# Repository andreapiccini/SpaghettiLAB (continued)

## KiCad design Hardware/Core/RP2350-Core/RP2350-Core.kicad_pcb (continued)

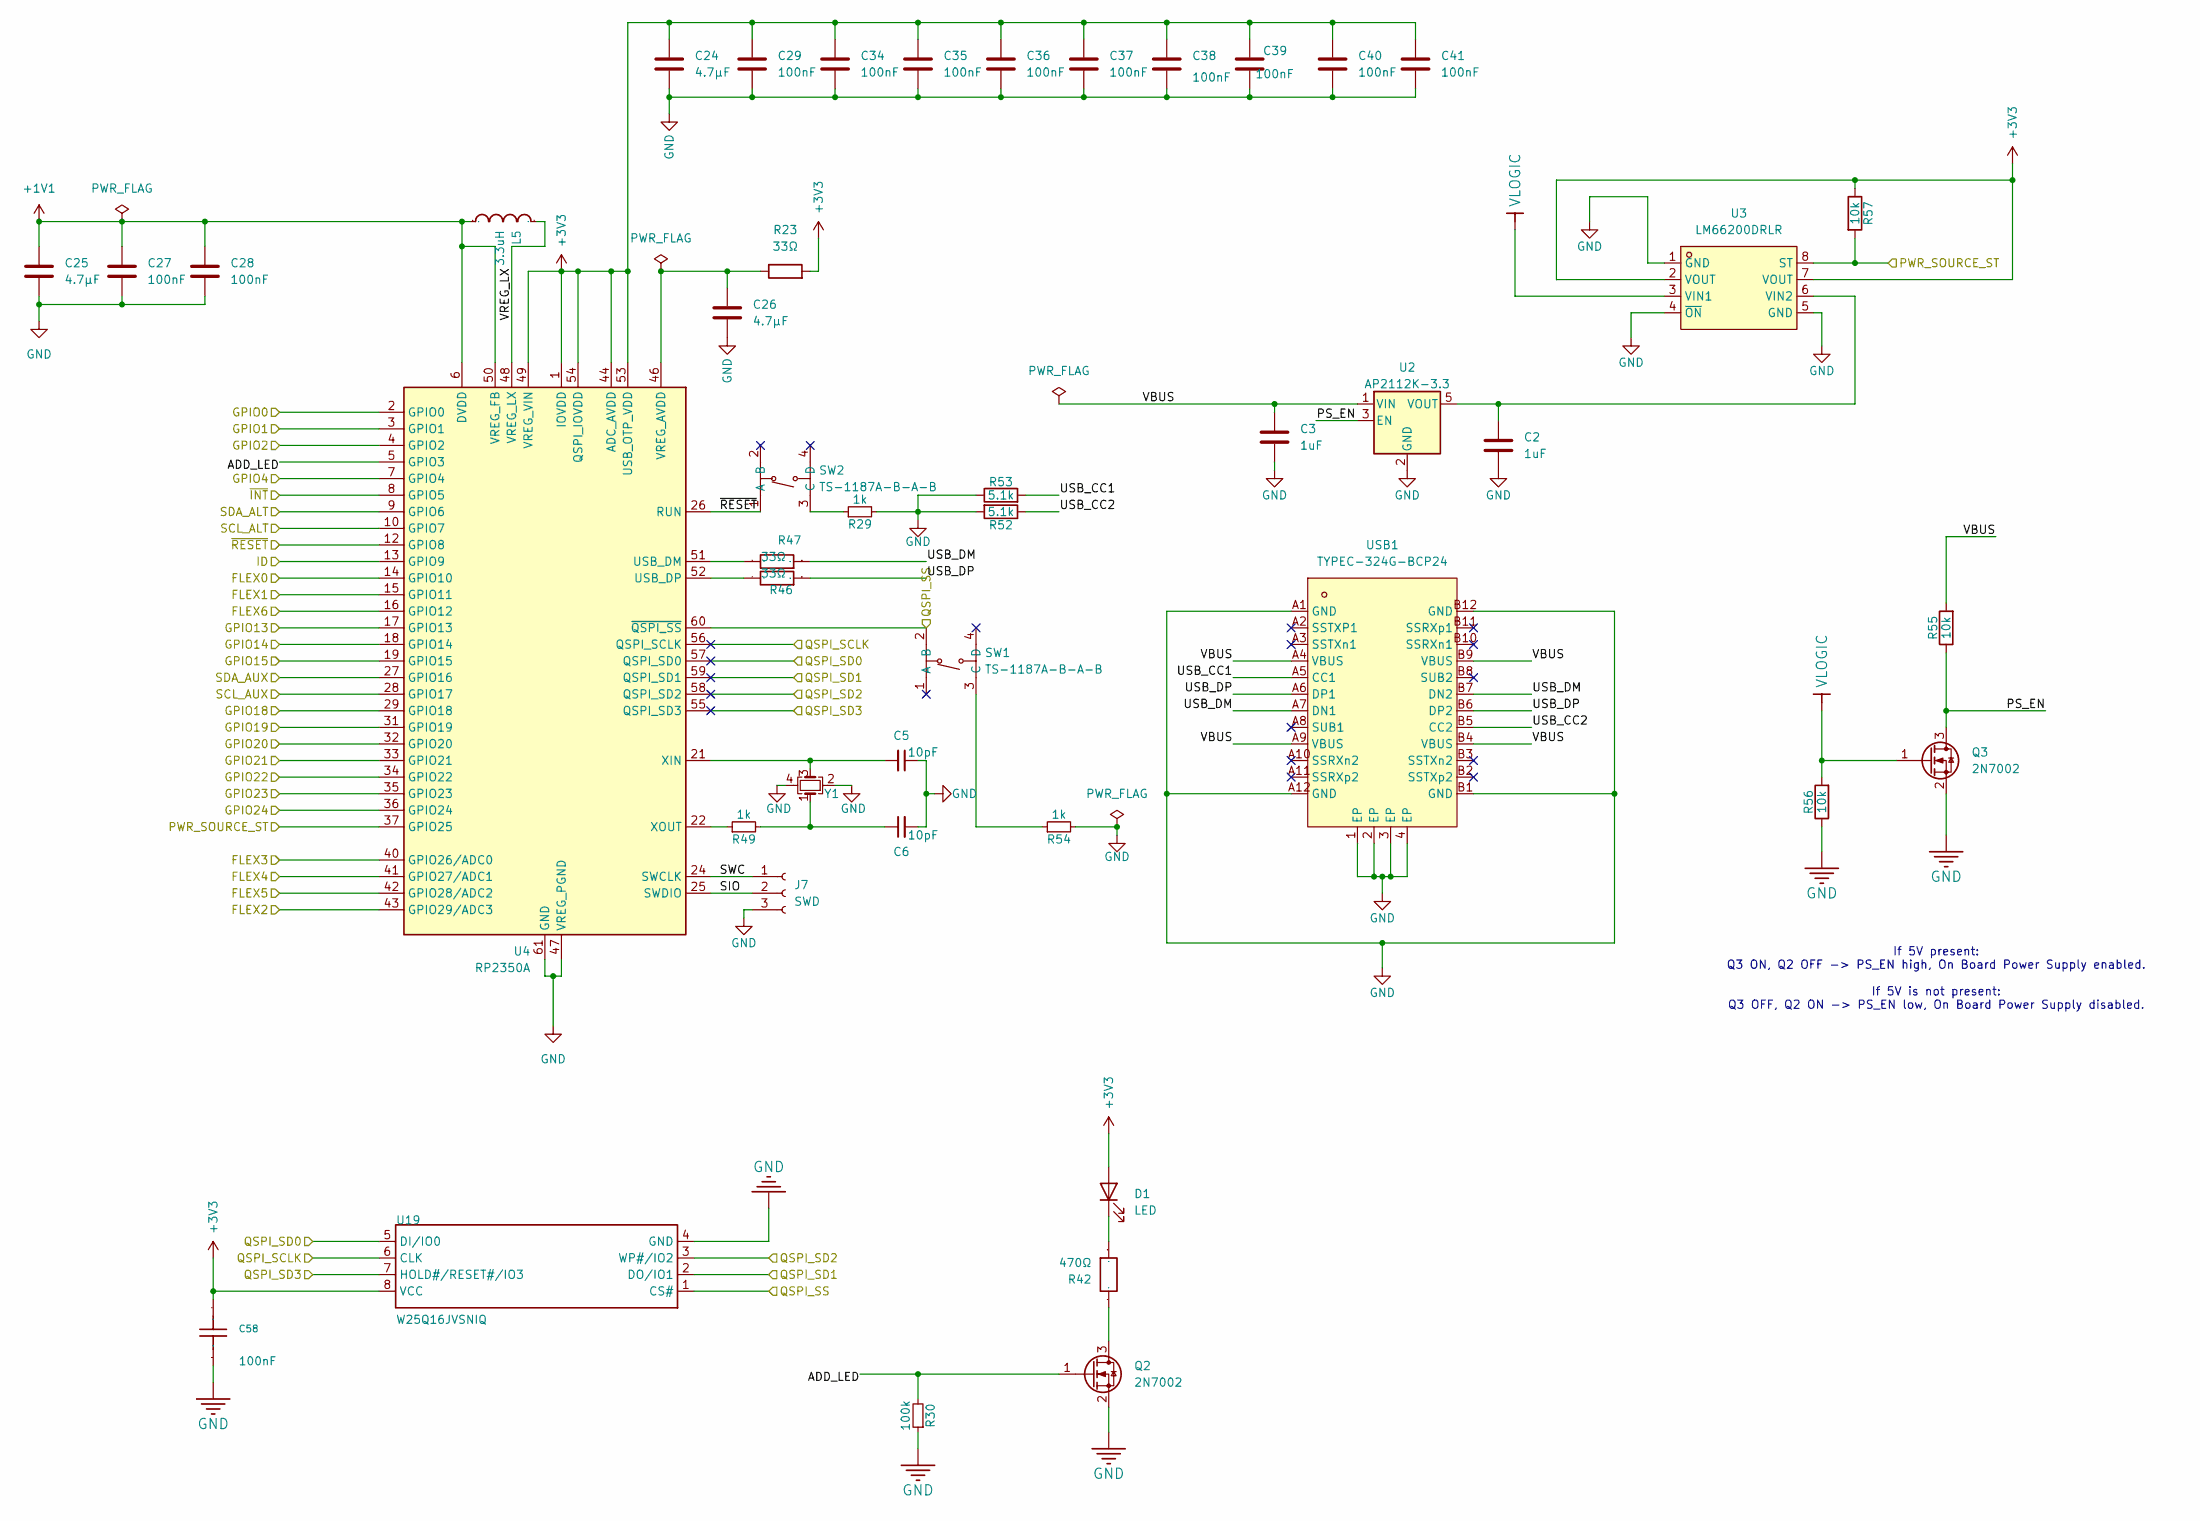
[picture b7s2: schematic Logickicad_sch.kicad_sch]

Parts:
C2, C3: 1uF; C0603; MPN CL05B104KA5NNNC
C5, C6: 10pF; C0603; MPN CL10C100JB8NFNC
C24, C25, C26: 4.7μF; C0603; MPN GRM155D80E475ME47J
C27, C28, C29, C34, C35, C36, C37, C38, C39, C40, C41: 100nF; C0603; MPN CL05B104KA5NNNC
C58: 100nF; C0603; Manufacturer Part 1206B104K500CT; LCSC Part Name 100nF ±10% 50V
D1: LED; LED0603-RD
J7: SWD; PinHeader_1x03_P1.27mm_Vertical
L5: 3.3uH; L1210; Manufacturer Part CMI322513U3R3KT; LCSC Part Name 3.3uH ±10%
Q2, Q3: 2N7002; SOT-23-3_L2.9-W1.3-P1.90-LS2.4-BR
R23: 33Ω; R0603; MPN RC0402FR-0733RL
R29, R49, R54: 1k; R0603; MPN RT0603FRE101KL
R30: 100k; R0603; MPN RT0603FRE101KL
R42: 470Ω; R0603; Manufacturer Part FRC0805J103TS; LCSC Part Name 10kΩ ±5% 125mW 厚膜电阻
R46, R47: 33Ω; R0603; Manufacturer Part CR0805F827R0G; LCSC Part Name 厚膜电阻 27Ω ±1% 125mW
R52, R53: 5.1k; R0603; MPN RC0402FR-075K1L
R55, R56, R57: 10k; R0603; MPN RC0402FR-075K1L
SW1, SW2: TS-1187A-B-A-B; SW-SMD_4P-L5.1-W5.1-P3.70-LS6.5-TL_H1.5; MPN TS-1187A-B-A-B; LCSC Part C318884
U2: AP2112K-3.3; SOT-25-5_L2.9-W1.6-P0.95-LS2.8-BL; MPN AP2112K-3.3TRG1
U3: LM66200DRLR; SOT-583-8_L2.1-W1.2-P0.50-LS1.6-BL; MPN LM66200DRLR; LCSC Part C3235556
U4: RP2350A; QFN-60_L7.0-W7.0-P0.40-TL-EP3.4
U19: W25Q16JVSNIQ; SOP-8_L4.9-W3.9-P1.27-LS6.0-BL; Manufacturer Part W25Q16JVSNIQ; LCSC Part Name 支持双/四路SPI接口的3V、16Mbit 串行闪存
USB1: TYPEC-324G-BCP24; USB-C-SMD_TYPEC-324G-BCP24; MPN TYPEC-324G-BCP24; LCSC Part C920230
Y1: Crystal; CRYSTAL-SMD_4P-L3.2-W2.5-BL; MPN ABM8-272-T3

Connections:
+1V1: C25.1, C27.2, C28.2, L5.1, U4.6 (DVDD), U4.23 (DVDD), U4.39 (DVDD), U4.50 (VREG_FB)
+3V3: C24.1, C29.2, C34.2, C35.2, C36.2, C37.2, C38.2, C39.2, C40.2, C41.2, C58.2, D1.2 (A), R23.2, R57.1, U3.2 (VOUT), U3.7 (VOUT), U4.1 (IOVDD), U4.11 (IOVDD), U4.20 (IOVDD), U4.30 (IOVDD), U4.38 (IOVDD), U4.44 (ADC_AVDD), U4.45 (IOVDD), U4.49 (VREG_VIN), U4.53 (USB_OTP_VDD), U4.54 (QSPI_IOVDD), U19.8 (VCC); also elsewhere on the board
/InOut (page 4)/FLEX0: U4.14 (GPIO10); also elsewhere on the board
/InOut (page 4)/FLEX1: U4.15 (GPIO11); also elsewhere on the board
/InOut (page 4)/FLEX2: U4.43 (GPIO29/ADC3); also elsewhere on the board
/InOut (page 4)/FLEX3: U4.40 (GPIO26/ADC0); also elsewhere on the board
/InOut (page 4)/FLEX4: U4.41 (GPIO27/ADC1); also elsewhere on the board
/InOut (page 4)/FLEX5: U4.42 (GPIO28/ADC2); also elsewhere on the board
/InOut (page 4)/FLEX6: U4.16 (GPIO12); also elsewhere on the board
/InOut (page 4)/GPIO0: U4.2 (GPIO0); also elsewhere on the board
/InOut (page 4)/GPIO1: U4.3 (GPIO1); also elsewhere on the board
/InOut (page 4)/GPIO2: U4.4 (GPIO2); also elsewhere on the board
/InOut (page 4)/GPIO4: U4.7 (GPIO4); also elsewhere on the board
/InOut (page 4)/GPIO13: U4.17 (GPIO13); also elsewhere on the board
/InOut (page 4)/GPIO14: U4.18 (GPIO14); also elsewhere on the board
/InOut (page 4)/GPIO15: U4.19 (GPIO15); also elsewhere on the board
/InOut (page 4)/GPIO18: U4.29 (GPIO18); also elsewhere on the board
/InOut (page 4)/GPIO19: U4.31 (GPIO19); also elsewhere on the board
/InOut (page 4)/GPIO20: U4.32 (GPIO20); also elsewhere on the board
/InOut (page 4)/GPIO21: U4.33 (GPIO21); also elsewhere on the board
/InOut (page 4)/GPIO22: U4.34 (GPIO22); also elsewhere on the board
/InOut (page 4)/GPIO23: U4.35 (GPIO23); also elsewhere on the board
/InOut (page 4)/GPIO24: U4.36 (GPIO24); also elsewhere on the board
/InOut (page 4)/ID: U4.13 (GPIO9); also elsewhere on the board
/InOut (page 4)/QSPI_SCLK: U4.56 (QSPI_SCLK), U19.6 (CLK); also elsewhere on the board
/InOut (page 4)/QSPI_SD0: U4.57 (QSPI_SD0), U19.5 (DI/IO0); also elsewhere on the board
/InOut (page 4)/QSPI_SD1: U4.59 (QSPI_SD1), U19.2 (DO/IO1); also elsewhere on the board
/InOut (page 4)/QSPI_SD2: U4.58 (QSPI_SD2), U19.3 (WP#/IO2); also elsewhere on the board
/InOut (page 4)/QSPI_SD3: U4.55 (QSPI_SD3), U19.7 (HOLD#/RESET#/IO3); also elsewhere on the board
/InOut (page 4)/QSPI_SS: SW1.2 (B), U4.60 (~QSPI_SS), U19.1 (CS#); also elsewhere on the board
/InOut (page 4)/SCL_ALT: U4.10 (GPIO7); also elsewhere on the board
/InOut (page 4)/SCL_AUX: U4.28 (GPIO17); also elsewhere on the board
/InOut (page 4)/SDA_ALT: U4.9 (GPIO6); also elsewhere on the board
/InOut (page 4)/SDA_AUX: U4.27 (GPIO16); also elsewhere on the board
/InOut (page 4)/~INT: U4.8 (GPIO5); also elsewhere on the board
/InOut (page 4)/~RESET: U4.12 (GPIO8); also elsewhere on the board
/Logic/ADD_LED: Q2.1 (G), R30.2, U4.5 (GPIO3)
/Logic/PS_EN: Q3.3 (D), R55.1, U2.3 (EN)
/Logic/PWR_SOURCE_ST: R57.2, U3.8 (ST), U4.37 (GPIO25)
/Logic/SIO: J7.2, U4.25 (SWDIO)
/Logic/SWC: J7.1, U4.24 (SWCLK)
/Logic/USB_CC1: R53.2, USB1.A5 (CC1)
/Logic/USB_CC2: R52.1, USB1.B5 (CC2)
/Logic/USB_DM: R47.1, USB1.A7 (DN1), USB1.B7 (DN2)
/Logic/USB_DP: R46.1, USB1.A6 (DP1), USB1.B6 (DP2)
/Logic/VBUS: C3.2, R55.2, U2.1 (VIN), USB1.A4 (VBUS), USB1.A9 (VBUS), USB1.B4 (VBUS), USB1.B9 (VBUS)
/Logic/VREG_LX: L5.2, U4.48 (VREG_LX)
GND: C2.1, C3.1, C5.1, C6.2, C24.2, C25.2, C26.2, C27.1, C28.1, C29.1, C34.1, C35.1, C36.1, C37.1, C38.1, C39.1, C40.1, C41.1, C58.1, J7.3, Q2.2 (S), Q3.2 (S), R29.2, R30.1, R52.2, R53.1, R54.2, R56.1, U2.2 (GND), U3.1 (GND), U3.4 (~ON), U3.5 (GND), U4.47 (VREG_PGND), U4.61 (GND), U19.4 (GND), USB1.1 (EP), USB1.2 (EP), USB1.3 (EP), USB1.4 (EP), USB1.A1 (GND), USB1.A12 (GND), USB1.B1 (GND), USB1.B12 (GND), Y1.2, Y1.4; also elsewhere on the board
unnamed: C6.1, R49.2, Y1.1
unnamed: D1.1 (K), R42.1
unnamed: Q2.3 (D), R42.2
unnamed: R54.1, SW1.3 (C)
unnamed: SW2.1 (A), U4.26 (RUN)
unnamed: R29.1, SW2.3 (C)
unnamed: C2.2, U2.5 (VOUT), U3.6 (VIN2)
unnamed: R47.2, U4.51 (USB_DM)
unnamed: R46.2, U4.52 (USB_DP)
unnamed: C26.1, R23.1, U4.46 (VREG_AVDD)
unnamed: C5.2, U4.21 (XIN), Y1.3
unnamed: R49.1, U4.22 (XOUT)
VLOGIC: Q3.1 (G), R56.2, U3.3 (VIN1); also elsewhere on the board

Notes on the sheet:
If 5V present: Q3 ON, Q2 OFF -> PS_EN high, On Board Power Supply enabled. If 5V is not present: Q3 OFF, Q2 ON -> PS_EN low, On Board Power Supply disabled.

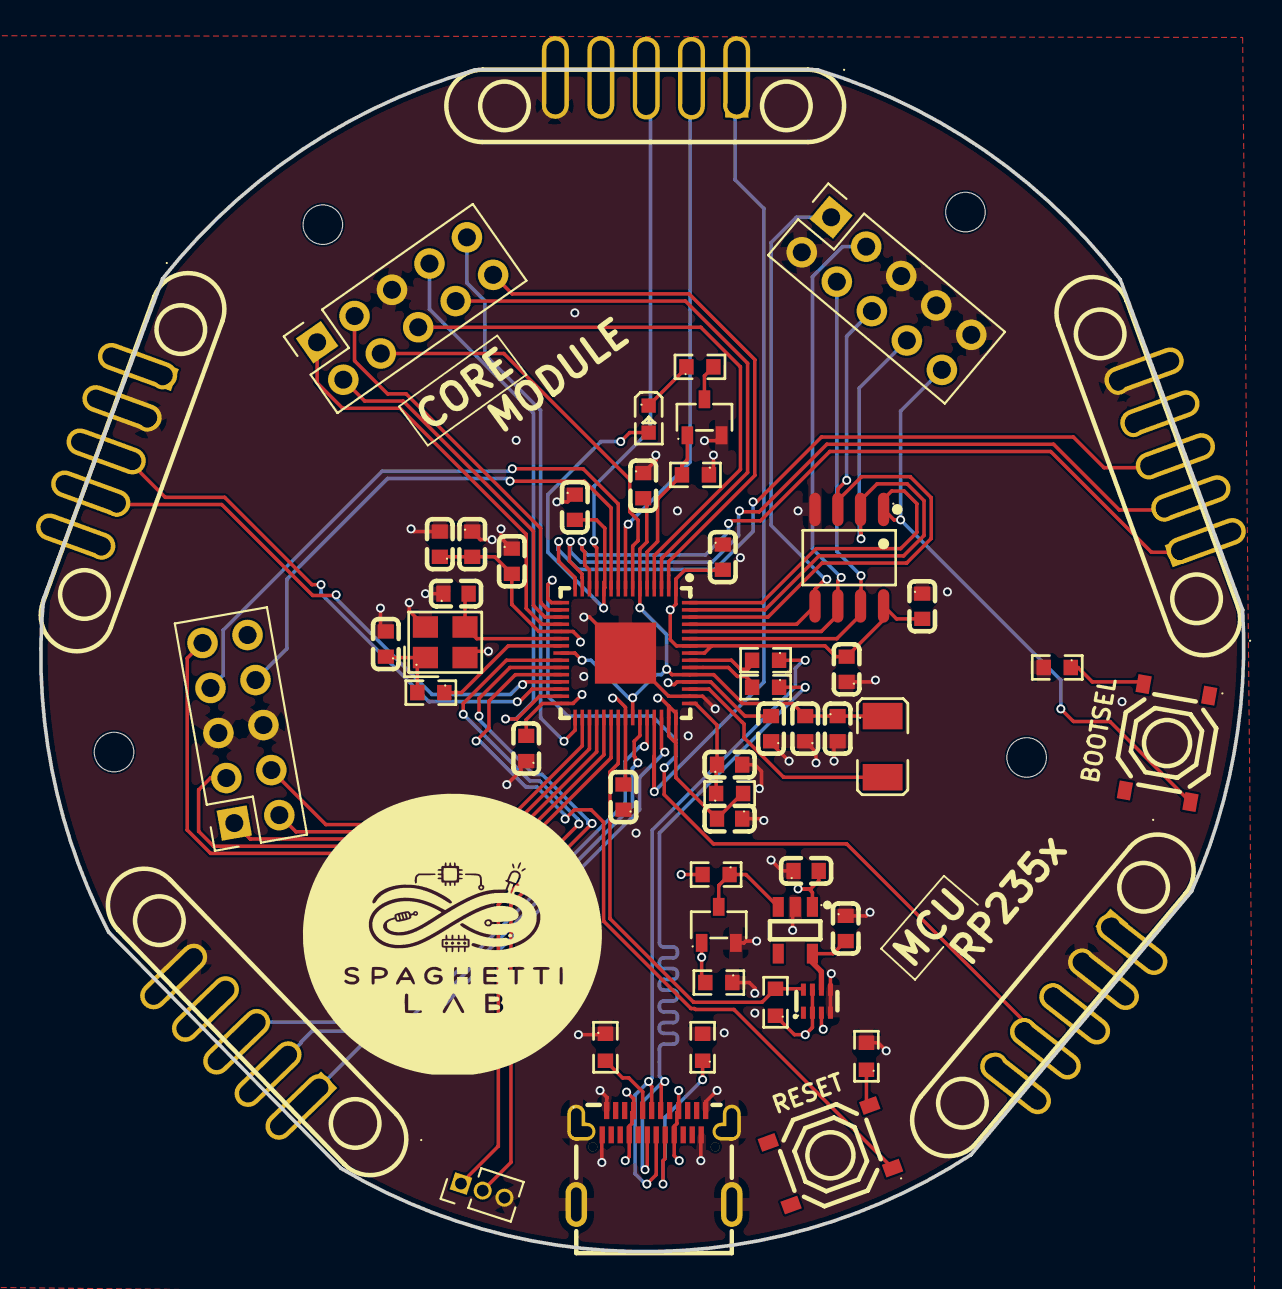
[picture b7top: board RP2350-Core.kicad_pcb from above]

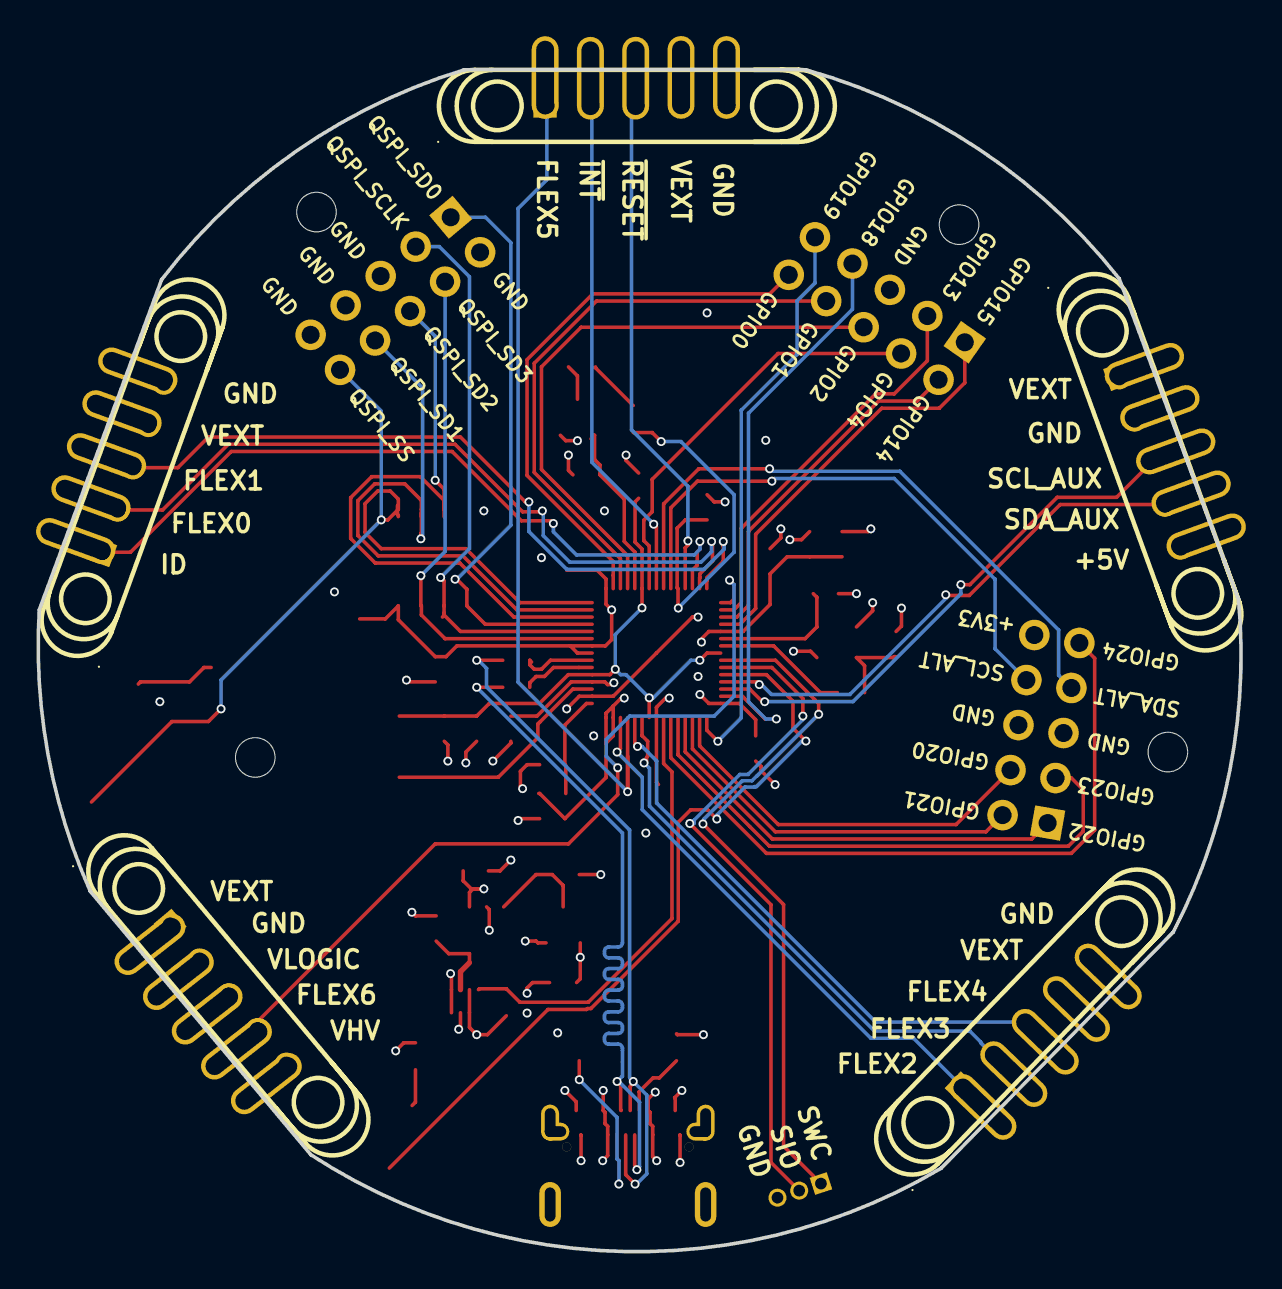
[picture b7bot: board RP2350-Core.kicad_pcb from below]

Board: 4 copper layers, 66.8 x 65.6 mm, 62 parts (5 on the bottom side), 64 nets.

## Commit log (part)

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2026-06-03 Create README.md for SpaghettiLAB project
    Added initial README.md with project overview and structure.
2026-06-03 Fix project name formatting in README
2026-06-04 Update logo image in README
2026-06-04 Fix image filename case in README.md
2026-06-05 Add TODO for output OR-ing and ideal diode stage
    Document the need for output OR-ing and ideal diode stage to enhance module safety and functionality.
2026-06-05 Update copyright year and owner in LICENSE file
2026-06-05 Add NOTICE file with project information and license
2026-06-05 Add CITATION.cff for SpaghettiLAB project
2026-06-05 Update LICENSE
2026-06-05 Create LICENSE
2026-06-05 Update and rename LICENSE to Software/LICENSE
2026-06-05 Create NOTICE
2026-06-05 Clean up license table formatting in README
    Removed extra whitespace in license table.
2026-06-06 Create RP2350-Core
2026-06-06 Create TODO
2026-06-06 Add RP2350 Core module Hardware
2026-06-06 Add expansion connector
2026-06-07 Reorganize RP2350 core project and add SpaghettiLAB shared libraries
2026-06-07 Added readme guide for impart gui
2026-06-09 Added RP2354 with integrated flash, 80 pin and OR diode in power supply
2026-06-09 Use shared SpaghettiLAB libraries with portable relative paths
2026-06-09 schematic done, missing pogo expansion pin component selection
2026-06-10 Footprint assigned core rp2350
2026-06-10 Created rp2354 and rp2350 variants
2026-06-10 Verison RP2350 with arduino header support
2026-06-10 Connectors connection improvements
2026-06-10 Added ADC TI ADS1115IDGSR to match arduino pinout and function and isolate arduino connections from spaghetti bus
2026-06-11 Placed footprints RP235x
2026-06-11 Use relative 3D model paths
2026-06-11 Refactor Core: remove Arduino/ADC support due to space constraints and fix portable 3D paths
2026-06-11 Routing core started
2026-06-12 Update README with website and newsletter links
    Added links to website and newsletter in README.
2026-06-12 Update newsletter link in README
2026-06-12 RP235X Layout complete
2026-06-15 Added toolchain config toolchain readme for /PD1002-DISH/RP2350, added bare minimum program fro RP2350
2026-06-18 completed RP235x pogo review
2026-06-18 Added labels on the board
2026-06-18 Resolved DRC
2026-06-18 Minor fix to footprints
2026-06-19 Removed N and S from footprint of pogo connectors
2026-06-20 New board: MS8313 motor driver FOC
2026-06-20 DRV8313 schematic done
2026-06-20 DRV8313 board done component assignment
2026-06-20 DRV8313 board JST 3-phase connector MP removed GND connection
2026-06-20 Added test point smaller for out current sense
2026-06-20 Minor fix to connectors footprint
2026-06-20 Placed edge and connector as SL standard
2026-06-20 fixes to magnetic connector position
2026-06-20 placed components
2026-06-21 Started routing and fixed flex label in core rp2350
2026-06-21 DRV8313 Layout ended
2026-06-21 DRC check ok
2026-06-21 Some minor fixes to silkscreen of all baords
2026-06-21 Fixes to ratnest of PD100W ATTENTION: not a definitve layout, print at your own risk
2026-06-23 added motor board project
2026-06-23 added bldc as5600 board
2026-06-24 started layout of encoder module
2026-06-24 Placed holes for motor mount
2026-06-24 Done layout for as5600 encoder board
2026-06-24 Added JST for UART to display module
2026-06-25 removed a jst in encoder board
2026-06-25 minor fix
2026-06-25 changed naming conventions for modules
2026-06-25 Changed naming convention to better match with spaghetti lab namings
